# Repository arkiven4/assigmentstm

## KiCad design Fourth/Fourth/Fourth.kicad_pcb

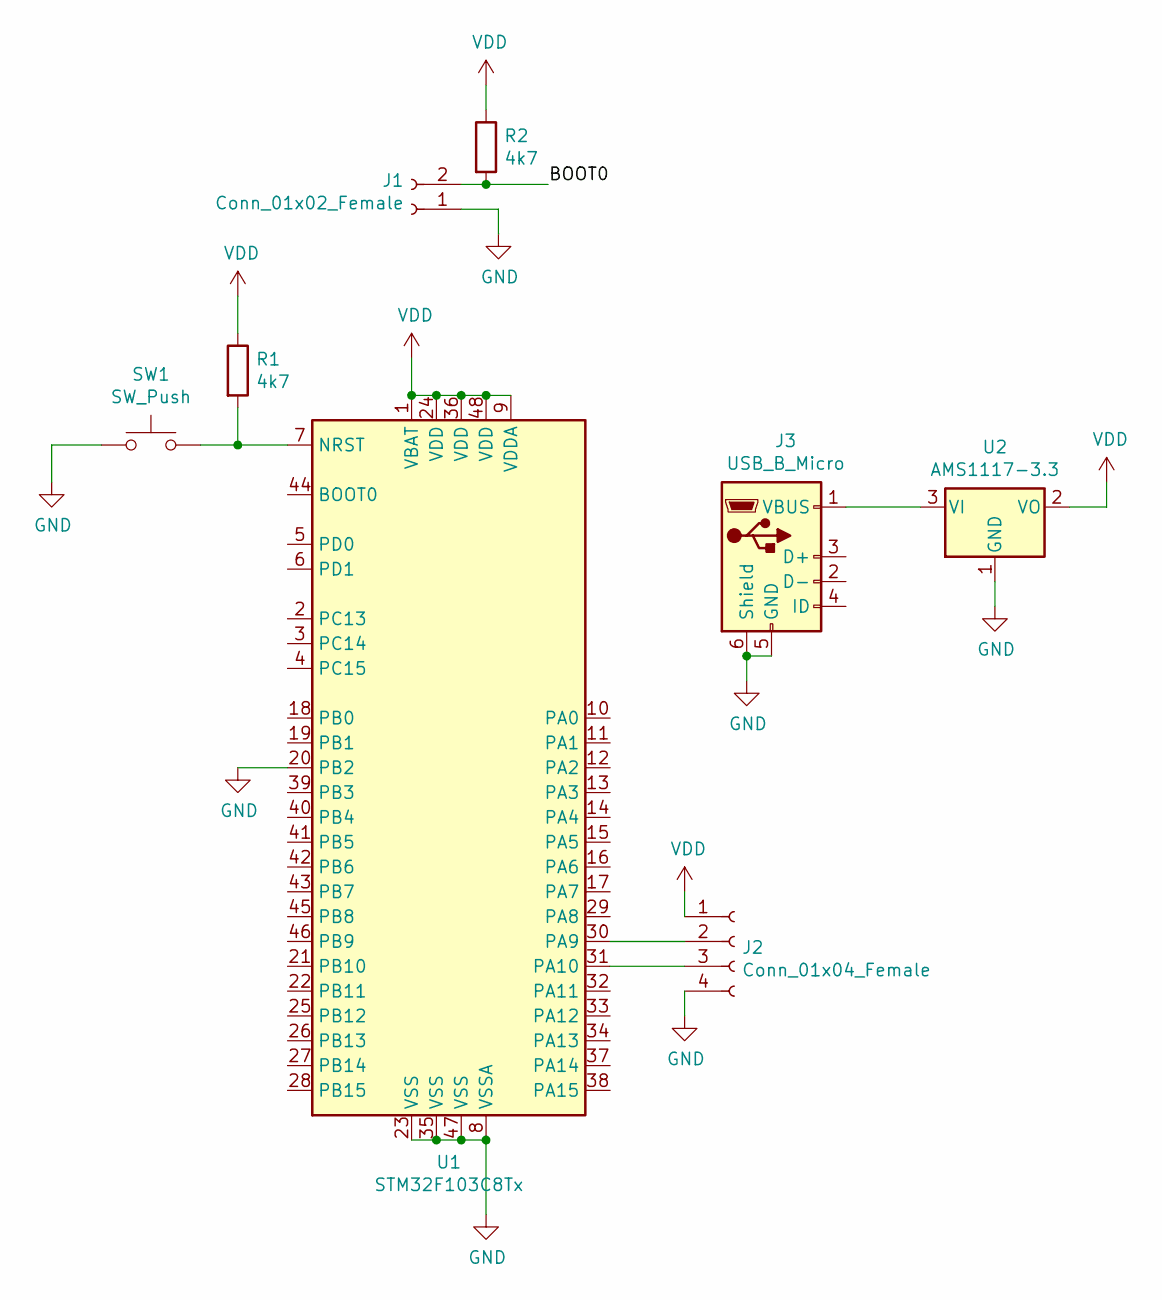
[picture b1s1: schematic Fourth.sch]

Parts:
J1: Conn_01x02_Female; PinHeader_1x02_P2.54mm_Vertical
J2: Conn_01x04_Female; PinHeader_1x04_P2.54mm_Vertical
J3: USB_B_Micro; USB_Micro-B_Amphenol_10103594-0001LF_Horizontal
R1, R2: 4k7; R_2512_6332Metric
SW1: SW_Push; SW_PUSH_6mm_H4.3mm
U1: STM32F103C8Tx; LQFP-48_7x7mm_P0.5mm
U2: AMS1117-3.3; SOT-223-3_TabPin2

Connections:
/BOOT0: J1.2, R2.2
GND: J1.1, J2.4, J3.5 (GND), J3.6 (Shield), SW1.1, U1.8 (VSSA), U1.20 (PB2), U1.23 (VSS), U1.35 (VSS), U1.47 (VSS), U2.1 (GND)
unnamed: J2.2, U1.30 (PA9)
unnamed: J2.3, U1.31 (PA10)
unnamed: J3.1 (VBUS), U2.3 (VI)
unnamed: R1.2, SW1.2, U1.7 (NRST)
VDD: J2.1, R1.1, R2.1, U1.1 (VBAT), U1.9 (VDDA), U1.24 (VDD), U1.36 (VDD), U1.48 (VDD), U2.2 (VO)

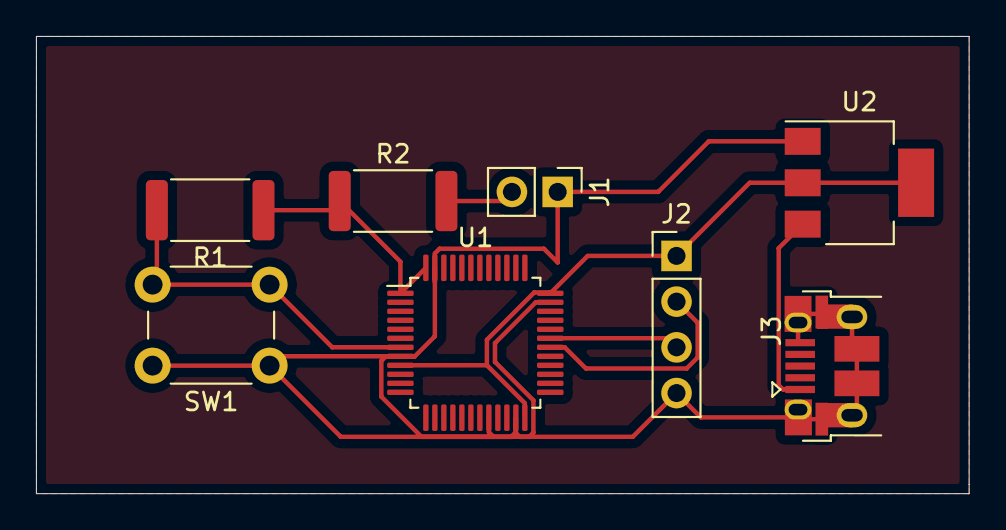
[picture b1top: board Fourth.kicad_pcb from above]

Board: 2 copper layers, 51.8 x 25.4 mm, 8 parts (0 on the bottom side), 7 nets.

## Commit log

2021-03-13 Upload
2021-03-13 Upload New
2021-03-15 Upload Fifth Assigment
